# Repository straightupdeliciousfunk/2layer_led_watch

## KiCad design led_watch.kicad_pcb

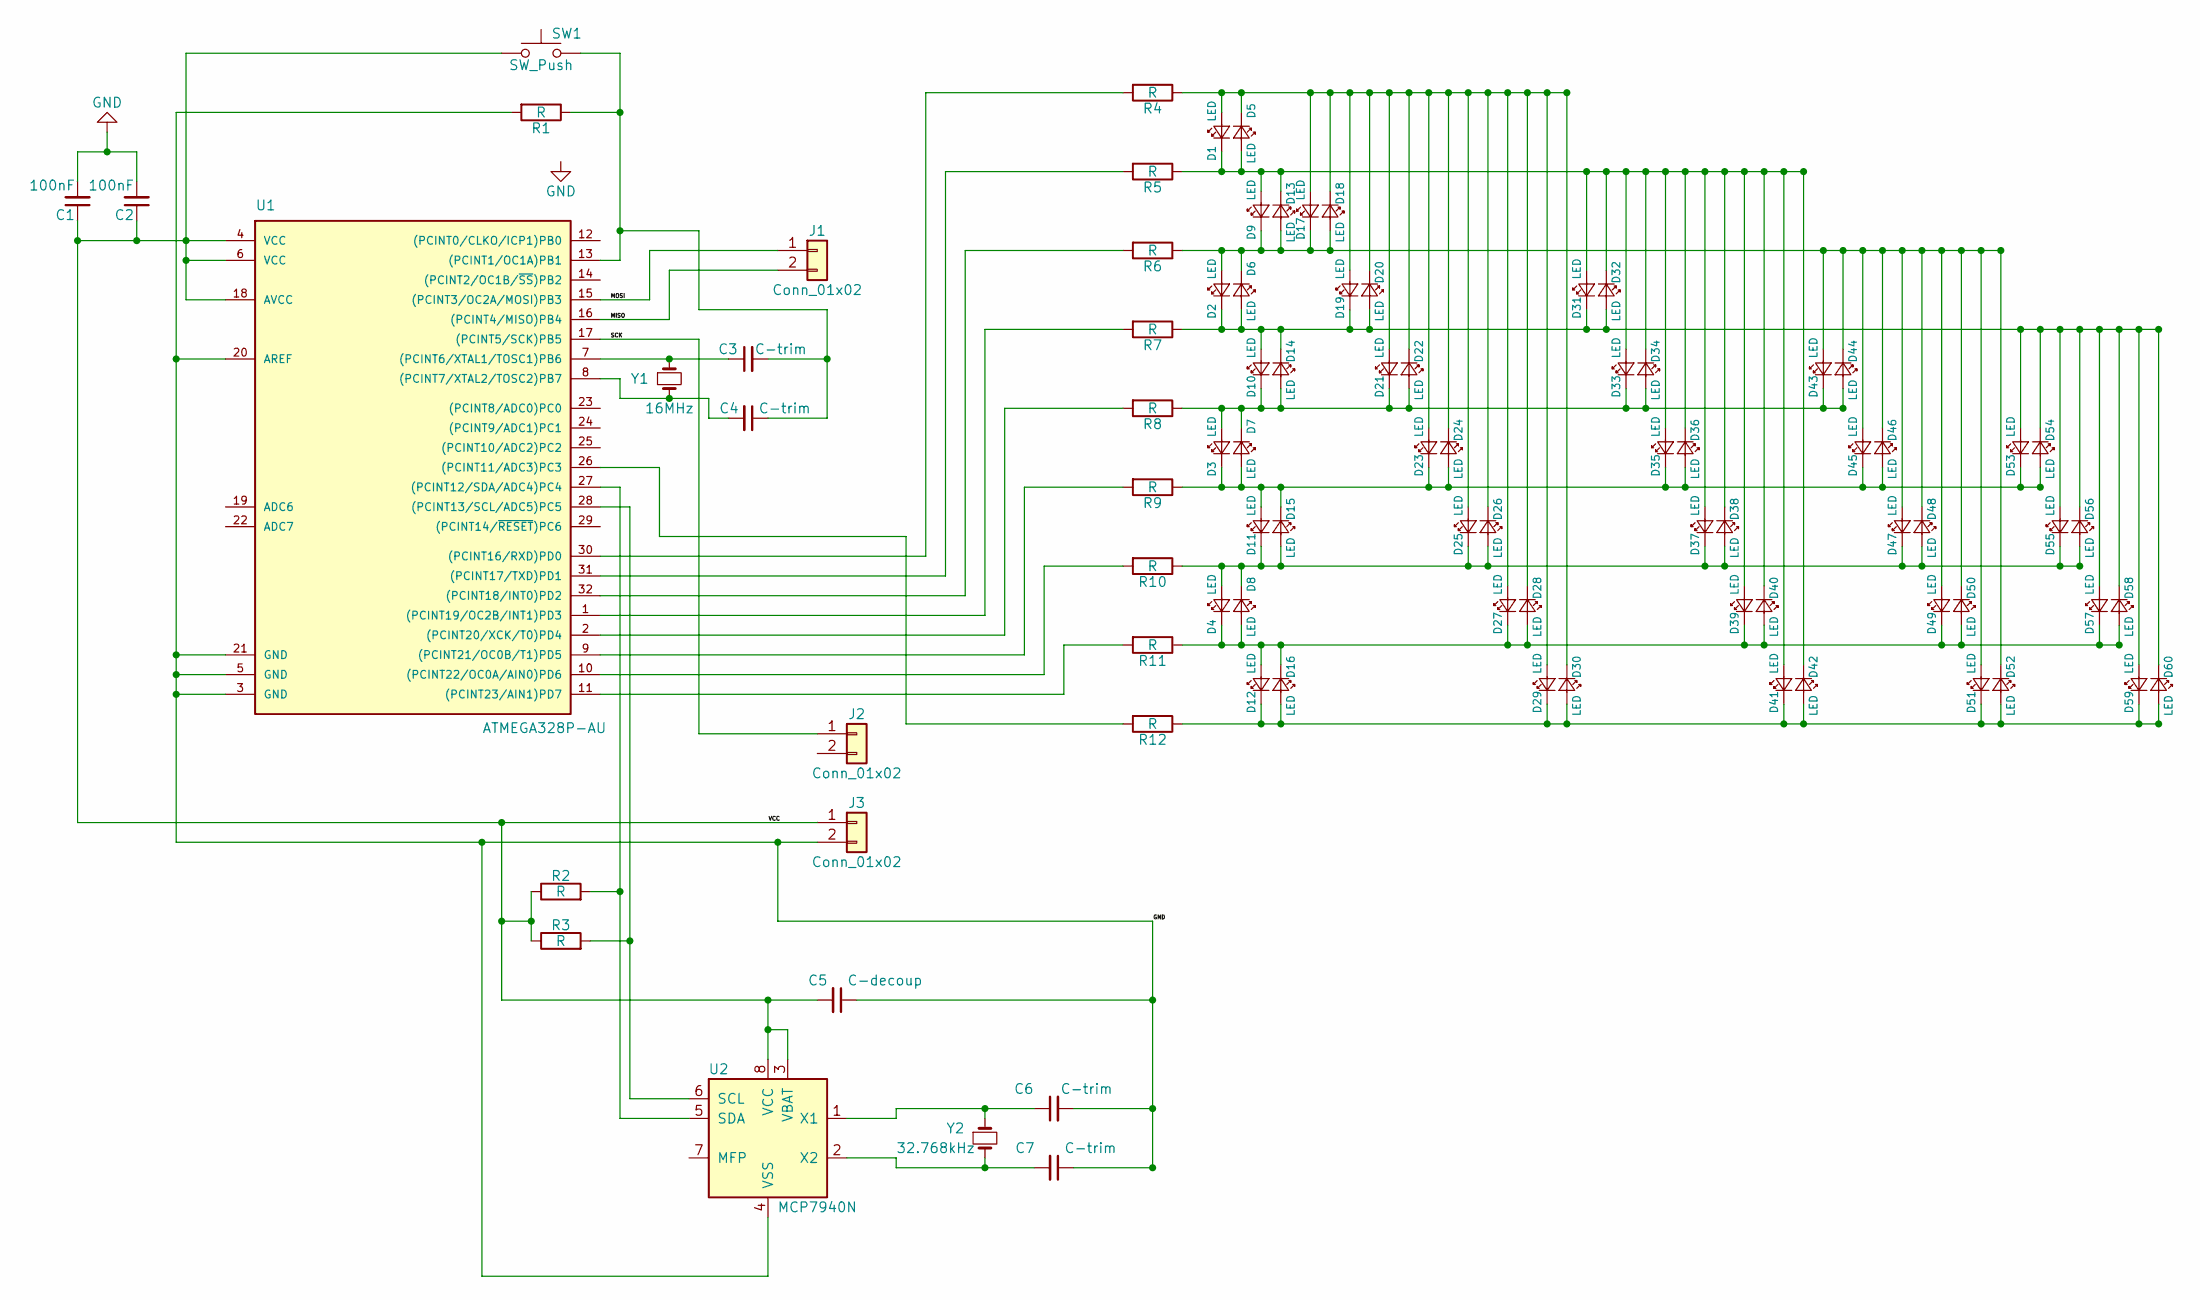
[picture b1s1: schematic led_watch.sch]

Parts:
C1, C2: 100nF; C_0603_HandSoldering
C3, C4, C6, C7: C-trim; C_0603_HandSoldering
C5: C-decoup; C_0603_HandSoldering
D1, D2, D3, D4, D5, D6, D7, D8, D9, D10, D11, D12, D13, D14, D15, D16, D17, D18, D19, D20, D21, D22, D23, D24, D25, D26, D27, D28, D29, D30, D31, D32, D33, D34, D35, D36, D37, D38, D39, D40, D41, D42, D43, D44, D45, D46, D47, D48, D49, D50, D51, D52, D53, D54, D55, D56, D57, D58, D59, D60: LED; LED_0603_HandSoldering
J1, J2, J3: Conn_01x02; Pin_Header_Straight_1x02_Pitch1.00mm
R1, R2, R3, R4, R5, R6, R7, R8, R9, R10, R11, R12: R; R_0603_HandSoldering
SW1: SW_Push; SW_SPST_B3U-1000P
U1: ATMEGA328P-AU; TQFP-32_7x7mm_Pitch0.8mm
U2: MCP7940N; SOIC-8-1EP_3.9x4.9mm_Pitch1.27mm
Y1: 16MHz; Crystal_SMD_2012-2pin_2.0x1.2mm_HandSoldering
Y2: 32.768kHz; Crystal_SMD_2012-2pin_2.0x1.2mm_HandSoldering

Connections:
/MISO: J1.2, U1.16 ((PCINT4/MISO)PB4)
/MOSI: J1.1, U1.15 ((PCINT3/OC2A/MOSI)PB3)
/SCK: J2.1, U1.17 ((PCINT5/SCK)PB5)
/VCC: C1.1, C2.1, C5.2, J3.1, R2.1, R3.1, SW1.1, U1.4 (VCC), U1.6 (VCC), U1.18 (AVCC), U2.3 (VBAT), U2.8 (VCC)
GND: C1.2, C2.2, C5.1, C6.2, C7.1, J3.2, R1.2, U1.3 (GND), U1.5 (GND), U1.20 (AREF), U1.21 (GND), U2.4 (VSS)
unnamed: C3.1, U1.7 ((PCINT6/XTAL1/TOSC1)PB6), Y1.1
unnamed: C3.2, C4.1, R1.1, SW1.2, U1.13 ((PCINT1/OC1A)PB1)
unnamed: C4.2, U1.8 ((PCINT7/XTAL2/TOSC2)PB7), Y1.2
unnamed: C6.1, U2.1 (X1), Y2.1
unnamed: C7.2, U2.2 (X2), Y2.2
unnamed: D1.1 (K), D5.2 (A), D9.2 (A), D13.1 (K), D31.2 (A), D32.1 (K), D33.2 (A), D34.1 (K), D35.2 (A), D36.1 (K), D37.2 (A), D38.1 (K), D39.2 (A), D40.1 (K), D41.2 (A), D42.1 (K), R5.1
unnamed: D1.2 (A), D5.1 (K), D17.2 (A), D18.1 (K), D19.2 (A), D20.1 (K), D21.2 (A), D22.1 (K), D23.2 (A), D24.1 (K), D25.2 (A), D26.1 (K), D27.2 (A), D28.1 (K), D29.2 (A), D30.1 (K), R4.1
unnamed: D3.2 (A), D7.1 (K), D10.1 (K), D14.2 (A), D21.1 (K), D22.2 (A), D33.1 (K), D34.2 (A), D43.1 (K), D44.2 (A), R8.1
unnamed: D2.1 (K), D6.2 (A), D10.2 (A), D14.1 (K), D19.1 (K), D20.2 (A), D31.1 (K), D32.2 (A), D53.2 (A), D54.1 (K), D55.2 (A), D56.1 (K), D57.2 (A), D58.1 (K), D59.2 (A), D60.1 (K), R7.1
unnamed: D4.2 (A), D8.1 (K), D11.1 (K), D15.2 (A), D25.1 (K), D26.2 (A), D37.1 (K), D38.2 (A), D47.1 (K), D48.2 (A), D55.1 (K), D56.2 (A), R10.1
unnamed: D3.1 (K), D7.2 (A), D11.2 (A), D15.1 (K), D23.1 (K), D24.2 (A), D35.1 (K), D36.2 (A), D45.1 (K), D46.2 (A), D53.1 (K), D54.2 (A), R9.1
unnamed: D12.1 (K), D16.2 (A), D29.1 (K), D30.2 (A), D41.1 (K), D42.2 (A), D51.1 (K), D52.2 (A), D59.1 (K), D60.2 (A), R12.1
unnamed: D4.1 (K), D8.2 (A), D12.2 (A), D16.1 (K), D27.1 (K), D28.2 (A), D39.1 (K), D40.2 (A), D49.1 (K), D50.2 (A), D57.1 (K), D58.2 (A), R11.1
unnamed: D2.2 (A), D6.1 (K), D9.1 (K), D13.2 (A), D17.1 (K), D18.2 (A), D43.2 (A), D44.1 (K), D45.2 (A), D46.1 (K), D47.2 (A), D48.1 (K), D49.2 (A), D50.1 (K), D51.2 (A), D52.1 (K), R6.1
unnamed: R2.2, U1.27 ((PCINT12/SDA/ADC4)PC4), U2.5 (SDA)
unnamed: R3.2, U1.28 ((PCINT13/SCL/ADC5)PC5), U2.6 (SCL)
unnamed: R4.2, U1.30 ((PCINT16/RXD)PD0)
unnamed: R5.2, U1.31 ((PCINT17/TXD)PD1)
unnamed: R6.2, U1.32 ((PCINT18/INT0)PD2)
unnamed: R7.2, U1.1 ((PCINT19/OC2B/INT1)PD3)
unnamed: R8.2, U1.2 ((PCINT20/XCK/T0)PD4)
unnamed: R9.2, U1.9 ((PCINT21/OC0B/T1)PD5)
unnamed: R10.2, U1.10 ((PCINT22/OC0A/AIN0)PD6)
unnamed: R11.2, U1.11 ((PCINT23/AIN1)PD7)
unnamed: R12.2, U1.26 ((PCINT11/ADC3)PC3)

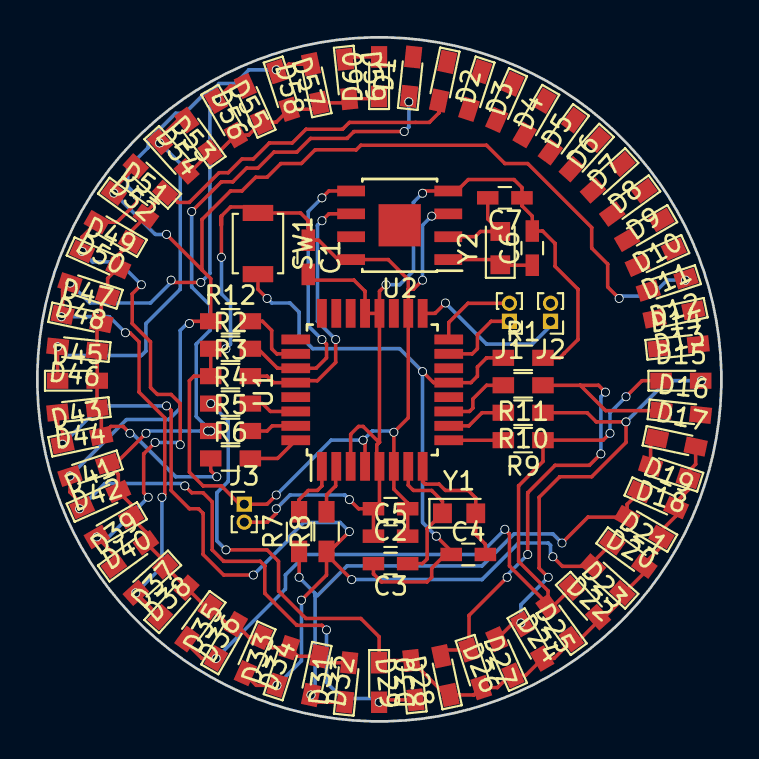
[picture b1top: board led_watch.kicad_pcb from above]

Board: 2 copper layers, 38.0 x 38.0 mm, 87 parts (0 on the bottom side), 30 nets.

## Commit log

2018-05-11 "holy s#@% it's friday" commit
2018-05-18 wiring
    started wiring up the outside leds. this is difficult.
